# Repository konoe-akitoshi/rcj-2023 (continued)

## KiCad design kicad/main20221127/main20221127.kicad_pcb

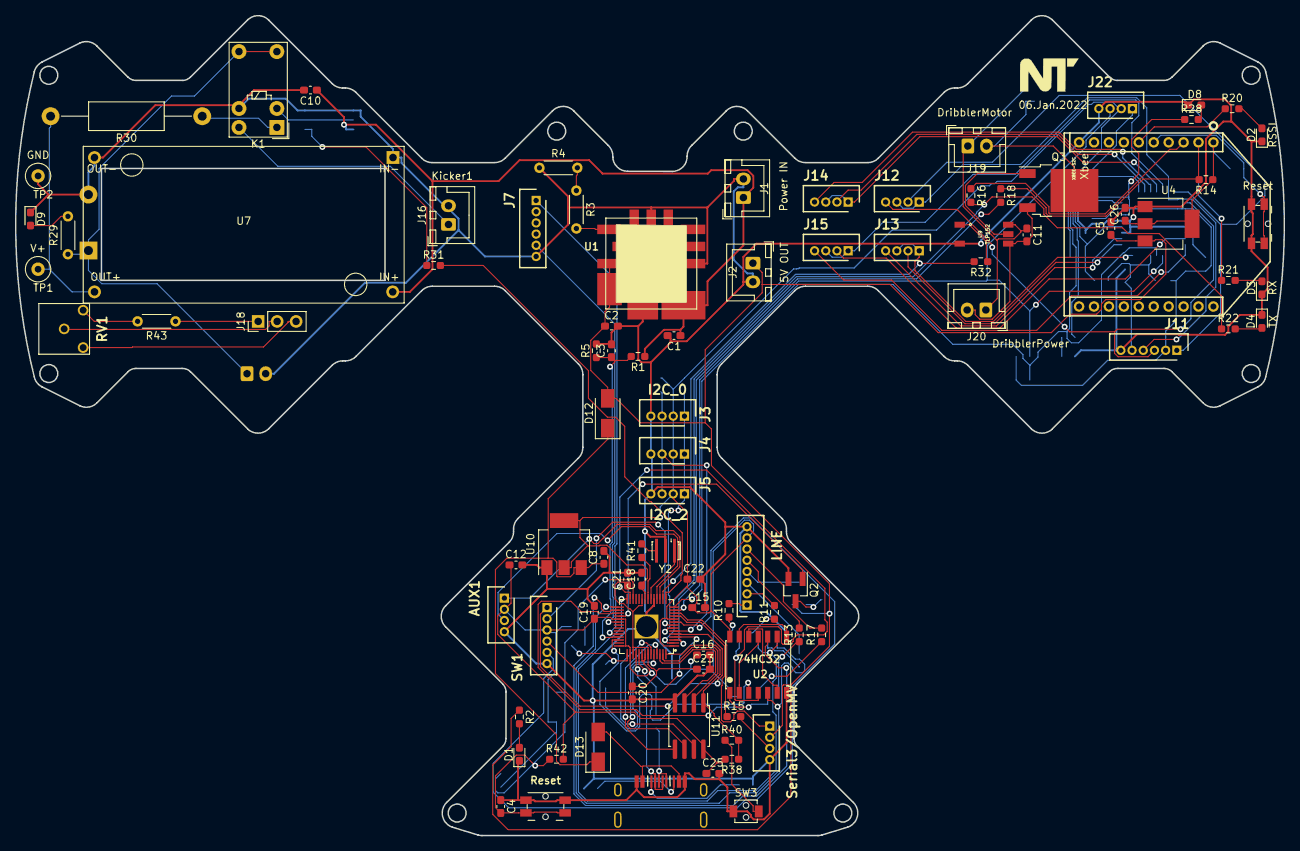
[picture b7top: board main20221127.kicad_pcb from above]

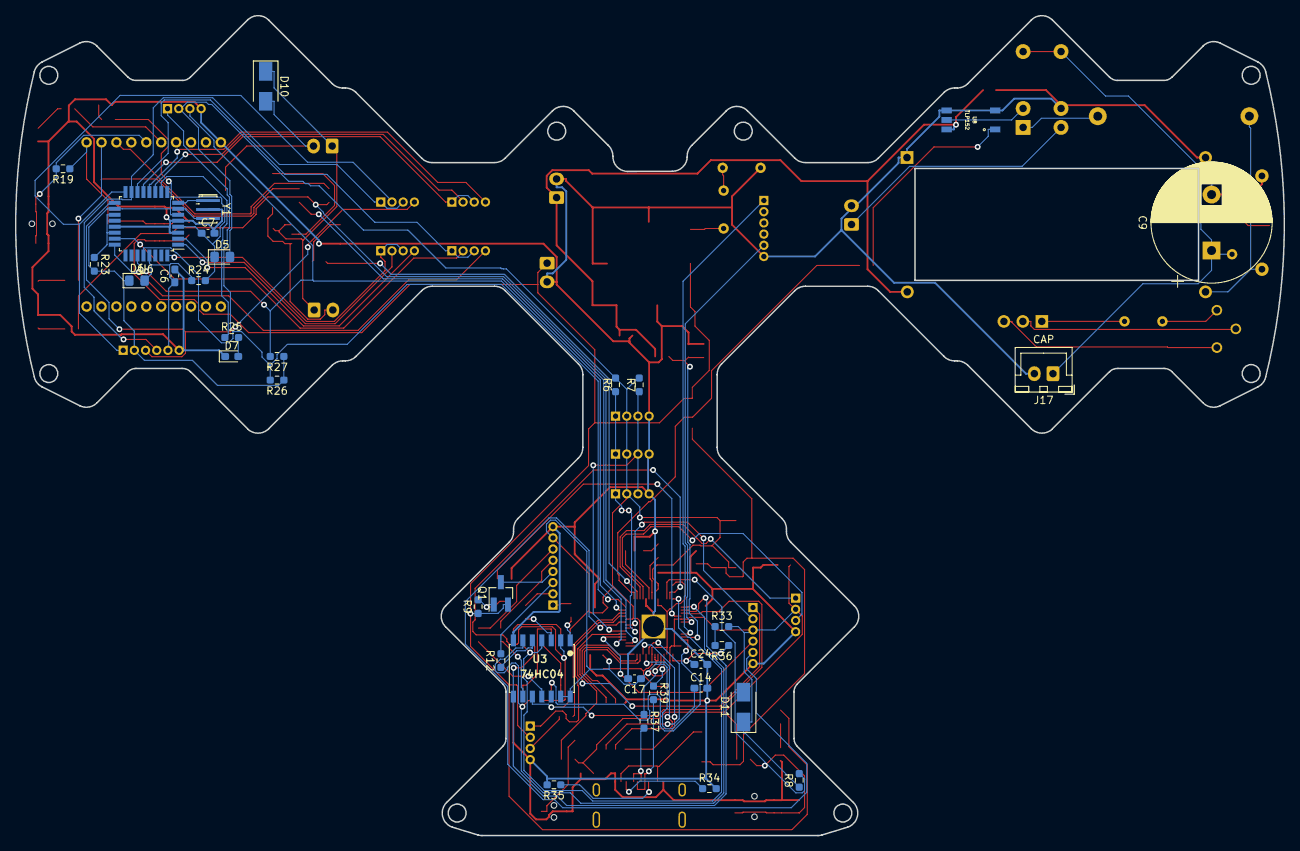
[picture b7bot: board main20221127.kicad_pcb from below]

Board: 2 copper layers, 170.0 x 109.9 mm, 127 parts (34 on the bottom side), 115 nets.

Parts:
C1, C2, C3, C4, C5, C6, C26: 10u; C_0603_1608Metric_Pad1.08x0.95mm_HandSolder
C7, C14, C15, C16, C17, C18, C19, C20, C21, C25: 0.1u; C_0603_1608Metric_Pad1.08x0.95mm_HandSolder
C8, C12: 10uF; C_0603_1608Metric_Pad1.08x0.95mm_HandSolder
C9: 2200uF/63V; CP_Radial_D16.0mm_P7.50mm
C10, C11, C22, C23, C24: 1uF; C_0603_1608Metric_Pad1.08x0.95mm_HandSolder
D1: LED; LED_SMLE13WBC8W1
D2: RSSI; LED_0603_1608Metric_Pad1.05x0.95mm_HandSolder
D3: RX; LED_0603_1608Metric_Pad1.05x0.95mm_HandSolder
D4: TX; LED_0603_1608Metric_Pad1.05x0.95mm_HandSolder
D5, D6: RSX101VAM-30TR; D_0805_2012Metric_Pad1.15x1.40mm_HandSolder
D7, D8: LED(OSWT1608); LED_0603_1608Metric_Pad1.05x0.95mm_HandSolder
D9: LED; LED_0603_1608Metric_Pad1.05x0.95mm_HandSolder
D10, D12, D13: SX34F; D_SMA
D11: RSX101VAM-30TR; D_SMA
J1: Power IN; JST_XH_B2B-XH-A_1x02_P2.50mm_Vertical
J2: 5V OUT; JST_XH_B2B-XH-A_1x02_P2.50mm_Vertical
J3: I2C_0; JSTB4B-ZR
J4: I2C_1; JSTB4B-ZR
J5: I2C_2; JSTB4B-ZR
J6: SW1; JSTB6B-ZR
J7: LED; JSTB6B-ZR
J8: AUX1; JSTB4B-ZR
J9: LINE; JSTB8B-ZR
J10: Serial3/OpenMV; JSTB4B-ZR
J11: ICSP; JSTB6B-ZR
J12: MD1; JSTB4B-ZR
J13: MD2; JSTB4B-ZR
J14: MD3; JSTB4B-ZR
J15: MD4; JSTB4B-ZR
J16: Kicker1; JST_XH_B2B-XH-A_1x02_P2.50mm_Vertical
J17: CAP; JST_XH_B2B-XH-A_1x02_P2.50mm_Vertical
J18: Conn_01x03; PinHeader_1x03_P2.54mm_Vertical
J19: DribblerMotor; JST_XH_B2B-XH-A_1x02_P2.50mm_Vertical
J20: DribblerPower; JST_XH_B2B-XH-A_1x02_P2.50mm_Vertical
J21: USB2.0_C_v3; USB-C-12-Pin-MidMount-ali-v4
J22: I2C_3; JSTB4B-ZR
K1: G5V-1/12V; Relay_SPDT_Omron_G5V-1
Q1: AO3401A; SOT-23_Handsoldering
Q2: AO3400A; SOT-23_Handsoldering
Q3: NP52N06SLG; TO-252-2
R1, R8, R23, R26, R27: 47k; R_0603_1608Metric_Pad0.98x0.95mm_HandSolder
R2, R20, R21, R22, R25, R28: 470; R_0603_1608Metric_Pad0.98x0.95mm_HandSolder
R3: 1k; R_Axial_DIN0204_L3.6mm_D1.6mm_P5.08mm_Horizontal
R4: 330; R_Axial_DIN0204_L3.6mm_D1.6mm_P5.08mm_Horizontal
R5, R6, R7, R9, R10, R11, R12, R13, R14, R15, R16, R17, R18, R19, R24: 10k; R_0603_1608Metric_Pad0.98x0.95mm_HandSolder
R29: 30k; R_Axial_DIN0204_L3.6mm_D1.6mm_P5.08mm_Horizontal
R30: 100; R_Axial_DIN0411_L9.9mm_D3.6mm_P20.32mm_Horizontal
R31, R32: 120; R_0603_1608Metric_Pad0.98x0.95mm_HandSolder
R33: 200R; R_0603_1608Metric_Pad0.98x0.95mm_HandSolder
R34, R35: 5.1kR; R_0603_1608Metric_Pad0.98x0.95mm_HandSolder
R36: 1R; R_0603_1608Metric_Pad0.98x0.95mm_HandSolder
R37, R39: 27.4R; R_0603_1608Metric_Pad0.98x0.95mm_HandSolder
R38: 10kR; R_0603_1608Metric_Pad0.98x0.95mm_HandSolder
R40: 1kR; R_0603_1608Metric_Pad0.98x0.95mm_HandSolder
R41, R42: 1k; R_0603_1608Metric_Pad0.98x0.95mm_HandSolder
R43: 200; R_Axial_DIN0204_L3.6mm_D1.6mm_P5.08mm_Horizontal
RV1: 20k; Trim-GF063X
SW1, SW2: Reset; THAU13-AB-R
SW3: BOOTSEL; TVAF06-A020B-R
TP1: V+; TestPoint_Loop_D2.60mm_Drill0.9mm_Beaded
TP2: GND; TestPoint_Loop_D2.60mm_Drill0.9mm_Beaded
U1: OKL-T_3-W12N-C; OKL-T3-W12N-C
U2: 74HC32; SOP14W
U3: 74HC04; SOP14W
U4, U10: AZ1117CH-3.3; SOT-223-3_TabPin2
U5: XBEE-S2C
U6: ATmega328P-AU; TQFP-32_7x7mm_P0.8mm
U7: XL6009/HW-432; XL6009_HW432
U8, U9: TLP152
U11: W25Q128JVS; W25Q16-128JV-SOIC
U12: RP2040; RP2040_hand
Y1: 8Mhz; Resonator_SMD_Murata_CSTxExxV-3Pin_3.0x1.1mm_HandSoldering
Y2: 12Mhz; Resonator_SMD_Murata_CSTxExxV-3Pin_3.0x1.1mm_HandSoldering

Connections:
+1V1: C20.1, C21.1, C23.1, U12.23 (DVDD), U12.45 (VREG_VOUT), U12.50 (DVDD)
+3.3VA: C7.1, D5.1 (K), D6.1 (K), J11.2, R23.2, R24.2, R26.1, R27.1, R28.1, U6.4 (VCC), U6.6 (VCC), U6.18 (AVCC)
+3V3: C12.1, C14.1, C15.1, C16.1, C17.1, C18.1, C19.1, C22.1, C25.1, D5.2 (A), D11.1 (K), J3.2, J4.2, J5.2, J6.3, J8.2, J9.7, J22.2, R6.1, R7.1, R8.1, R33.2, R38.2, R42.2, U2.14 (VCC), U3.13, U3.14 (VCC), U10.2 (VO), U11.8 (VCC), U12.1 (IOVDD), U12.10 (IOVDD), U12.22 (IOVDD), U12.33 (IOVDD), U12.42 (IOVDD), U12.44 (VREG_IN), U12.48 (USB_VDD), U12.49 (IOVDD)
+5V: C2.1, C5.1, D12.2 (A), J2.1, J10.2, Q1.2 (S), R2.1, R9.1, U1.4 (VOUT), U1.5 (SENSE), U4.3 (VI)
+15V: C1.1, C10.1, J1.1, R1.1, U1.2 (VIN), U7.2 (+VIN), U8.6 (VCC)
/Sheet61861092/drib_in: R32.2, U12.16 (GPIO13)
/Sheet61861092/kick_in: R31.2, U12.15 (GPIO12)
/Sheet63625160/SCL_1: J22.1, R26.2, U6.28 (PC5), U12.14 (GPIO11)
/Sheet63625160/SDA_1: J22.3, R27.2, U6.27 (PC4), U12.13 (GPIO10)
/rp2040/GPIO00/01: R16.2, R22.1, U12.2 (GPIO0)
/rp2040/GPIO01/02: R18.2, U12.3 (GPIO1)
/rp2040/GPIO02/04: J6.4, U12.4 (GPIO2)
/rp2040/GPIO03/05: J6.1, U12.5 (GPIO3)
/rp2040/GPIO04/06: J3.3, J4.3, J5.3, R7.2, U12.6 (GPIO4)
/rp2040/GPIO05/07: J3.1, J4.1, J5.1, R6.2, U12.7 (GPIO5)
/rp2040/GPIO06/09: J6.2, U12.8 (GPIO6)
/rp2040/GPIO07/10: J6.5, U12.9 (GPIO7)
/rp2040/GPIO08/11: J10.1, U12.11 (GPIO8)
/rp2040/GPIO09/12: R15.1, U12.12 (GPIO9)
/rp2040/GPIO14/19: J8.1, U12.17 (GPIO14)
/rp2040/GPIO15/20: J8.3, U12.18 (GPIO15)
/rp2040/GPIO16/21: U2.4, U3.2, U12.27 (GPIO16)
/rp2040/GPIO17/22: U2.9, U3.4, U12.28 (GPIO17)
/rp2040/GPIO18/24: U2.5, U3.6, U12.29 (GPIO18)
/rp2040/GPIO19/25: U2.10, U3.8, U12.30 (GPIO19)
/rp2040/GPIO20/26: U2.1, U3.10, U12.31 (GPIO20)
/rp2040/GPIO21/27: Q2.1 (G), U12.32 (GPIO21)
/rp2040/GPIO22/29: J7.5, U12.34 (GPIO22)
/rp2040/GPIO26/31: J7.1, U12.38 (GPIO26_ADC0)
/rp2040/GPIO28/34: U2.3, U12.40 (GPIO28_ADC2)
/rp2040/RUN(RES)/30: C4.2, D11.2 (A), R8.2, R42.1, SW1.1, U12.26 (RUN)
ADC_VREF: R33.1, R36.2
GND: C1.2, C2.2, C3.2, C4.1, C5.2, C6.2, C7.2, C8.2, C9.2, C10.2, C12.2, C14.2, C15.2, C16.2, C17.2, C18.2, C19.2, C20.2, C21.2, C22.2, C23.2, C24.2, C25.2, C26.2, D1.1 (K), D2.1 (K), D3.1 (K), D4.1 (K), D7.1 (K), D8.1 (K), D9.1 (K), J1.2, J2.2, J3.4, J4.4, J5.4, J6.6, J7.6, J8.4, J9.8, J10.4, J11.6, J16.2, J17.2, J21.4 (GND), J22.4, K1.9, Q2.2 (S), R4.1, R5.2, R34.2, R35.2, SW1.2, SW2.2, SW3.1, TP2.1, U1.1 (ON/OFF), U1.3 (GND_1), U1.7 (GND_2), U2.7 (GND), U3.7 (GND), U4.1 (GND), U5.10 (GND), U6.3 (GND), U6.5 (GND), U6.21 (GND), U7.1 (-VIN), U7.3 (-VOUT), U8.3, U8.4 (GND), U9.3, U10.1 (GND), U11.4 (GND), U12.19 (TESTEN), U12.57 (GND), Y1.2, Y2.2
unnamed: C6.1, D6.2 (A), J11.5, R24.1, U6.29 (~RESET/PC6)
unnamed: C8.1, D12.1 (K), D13.1 (K), U10.3 (VI)
unnamed: C9.1, J17.1, K1.5, K1.6, R29.1
unnamed: C11.1, D10.1 (K), J19.1, J20.1, U9.6 (VCC)
unnamed: C11.2, J20.2, Q3.3 (S), U9.4 (GND)
unnamed: C24.1, R36.1, U12.43 (ADC_AVDD)
unnamed: C26.1, R14.1, R19.1, U4.2 (VO), U5.1 (VDD)
unnamed: D1.2 (A), R2.2
unnamed: D2.2 (A), R20.2
unnamed: D3.2 (A), R21.2
unnamed: D4.2 (A), R22.2
unnamed: D7.2 (A), R25.2
unnamed: D8.2 (A), R28.2
unnamed: D9.2 (A), R29.2
unnamed: D10.2 (A), J19.2, Q3.2 (D)
unnamed: D13.2 (A), J21.1 (VBUS)
unnamed: J9.1, R10.2
unnamed: J9.2, R11.2
unnamed: J9.3, R12.2
unnamed: J9.4, Q1.3 (D)
unnamed: J9.5, R13.2
unnamed: J9.6, R17.2
unnamed: J10.3, R15.2
unnamed: J11.1, J12.2, U6.16 (PB4)
unnamed: J11.3, J12.4, U6.17 (PB5)
unnamed: J11.4, J12.1, J12.3, U6.15 (PB3)
unnamed: J13.1, J13.3, U6.32 (PD2)
unnamed: J13.2, U6.1 (PD3)
unnamed: J13.4, U6.2 (PD4)
unnamed: J14.1, J14.3, U6.13 (PB1)
unnamed: J14.2, U6.11 (PD7)
unnamed: J14.4, U6.12 (PB0)
unnamed: J15.1, J15.3, U6.14 (PB2)
unnamed: J15.2, U6.23 (PC0)
unnamed: J15.4, U6.24 (PC1)
unnamed: J16.1, K1.10
unnamed: J18.1, R43.1
unnamed: J18.2, RV1.2
unnamed: J18.3, RV1.3
unnamed: J21.5 (CC1), R35.1
unnamed: J21.6 (CC2), R34.1
unnamed: K1.1, R30.1
unnamed: K1.2, U8.5 (VO)
unnamed: Q1.1 (G), Q2.3 (D), R9.2
unnamed: Q3.1 (G), U9.5 (VO)
unnamed: R3.1, R4.2
unnamed: R3.2, U1.6 (TRIM)
unnamed: R10.1, U3.1
unnamed: R11.1, U3.3
unnamed: R12.1, U3.5
unnamed: R13.1, U3.9
unnamed: R14.2, R18.1, R21.1, U5.2 (DOUT)
unnamed: R16.1, U5.3 (DIN)
unnamed: R17.1, U3.11
unnamed: R19.2, SW2.1, U5.5 (RESET)
unnamed: R20.1, U5.6 (RSSI)
unnamed: R23.1, U6.19 (ADC6), U6.22 (ADC7)
unnamed: R25.1, U6.10 (PD6)
unnamed: R30.2, TP1.1, U7.4 (+VOUT)
unnamed: R31.1, U8.1
unnamed: R32.1, U9.1
unnamed: R37.1, U12.47 (USB_DP)
unnamed: R39.1, U12.46 (USB_DM)
unnamed: R40.1, SW3.2
unnamed: R41.1, U12.21 (XOUT)
unnamed: R41.2, Y2.3
unnamed: R43.2, RV1.1
unnamed: U2.2, U2.11
unnamed: U2.6, U2.12
unnamed: U2.8, U2.13
unnamed: U6.7 (XTAL1/PB6), Y1.3
unnamed: U6.8 (XTAL2/PB7), Y1.1
unnamed: U12.20 (XIN), Y2.1
QSPI_CLK: U11.6 (CLK), U12.52 (QSPI_SCLK)
QSPI_SD0: U11.5 (DI(IO0)), U12.53 (QSPI_SD0)
QSPI_SD1: U11.2 (DO(IO1)), U12.55 (QSPI_SD1)
QSPI_SD2: U11.3 (IO2), U12.54 (QSPI_SD2)
QSPI_SD3: U11.7 (IO3), U12.51 (QSPI_SD3)
QSPI_SS: R38.1, R40.2, U11.1 (~CS), U12.56 (QSPI_SS)
USB_DM: J21.2 (D-), R39.2
USB_DP: J21.3 (D+), R37.2
Vbatt: C3.1, R1.2, R5.1, U12.39 (GPIO27_ADC1)

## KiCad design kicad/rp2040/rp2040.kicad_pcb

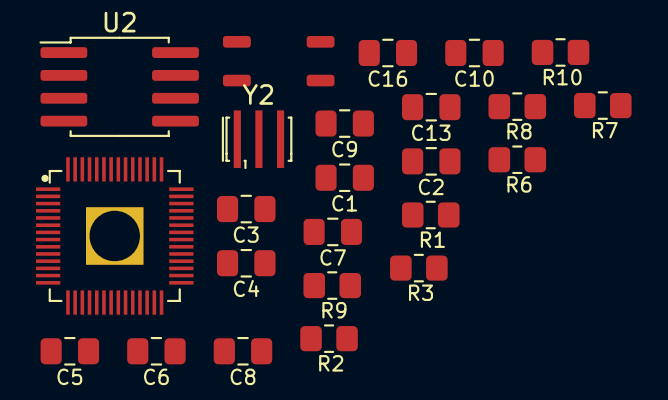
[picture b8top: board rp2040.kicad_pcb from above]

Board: 2 copper layers, 24 parts (0 on the bottom side), 18 nets, no tracks yet.

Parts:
C1, C2, C4, C6, C7, C8, C10, C13, C16: 100nF; Capacitor_0805_2012
C3, C5, C9: 1uF; Capacitor_0805_2012
R1, R2: 27.4R; Register_0805_2012
R3, R6, R7: 1kR; Register_0805_2012
R8: 10kR; Register_0805_2012
R9: 200R; Register_0805_2012
R10: 1R; Register_0805_2012
SW1: SW_Push; SKRPABE010
U1: RP2040; RP2040_hand
U2: W25Q128JVS; W25Q16-128JV-SOIC
Y2: 12Mhz; Resonator_SMD_Murata_CSTxExxV-3Pin_3.0x1.1mm_HandSoldering

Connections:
+1V1: C1.1, C2.1, C3.1, U1.23 (DVDD), U1.45 (VREG_VOUT), U1.50 (DVDD)
+3V3: C4.1, C5.1, C6.1, C7.1, C8.1, C10.1, C13.1, C16.1, R7.2, R8.2, R9.2, U1.1 (IOVDD), U1.10 (IOVDD), U1.22 (IOVDD), U1.33 (IOVDD), U1.42 (IOVDD), U1.44 (VREG_IN), U1.48 (USB_VDD), U1.49 (IOVDD), U2.8 (VCC)
/RUN(RES)/30: R7.1, U1.26 (RUN)
ADC_VREF: R9.1, R10.2
GND: C1.2, C2.2, C3.2, C4.2, C5.2, C6.2, C7.2, C8.2, C9.2, C10.2, C13.2, C16.2, SW1.1, U1.19 (TESTEN), U1.57 (GND), U2.4 (GND), Y2.2
unnamed: C9.1, R10.1, U1.43 (ADC_AVDD)
unnamed: R1.1, U1.47 (USB_DP)
unnamed: R2.1, U1.46 (USB_DM)
unnamed: R3.1, SW1.2
unnamed: R6.1, U1.21 (XOUT)
unnamed: R6.2, Y2.3
unnamed: U1.20 (XIN), Y2.1
QSPI_CLK: U1.52 (QSPI_SCLK), U2.6 (CLK)
QSPI_SD0: U1.53 (QSPI_SD0), U2.5 (DI(IO0))
QSPI_SD1: U1.55 (QSPI_SD1), U2.2 (DO(IO1))
QSPI_SD2: U1.54 (QSPI_SD2), U2.3 (IO2)
QSPI_SD3: U1.51 (QSPI_SD3), U2.7 (IO3)
QSPI_SS: R3.2, R8.1, U1.56 (QSPI_SS), U2.1 (~CS)

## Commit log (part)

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2022-11-04 originaldata
2022-11-07 chore: update README.md
2022-11-07 chore: fix typo in README.md
2022-11-08 refactor: rename main program directory
    ディレクトリの階層も変更してる
2022-11-08 chore: add .gitignore
2022-11-08 style: format by clang-format
2022-11-08 style: fix format by manual
2022-11-10 pcb rp2040test
2022-11-11 Tof 基板起こし
2022-11-14 chore: delete kicad
2022-11-16 chore: add local include files
2022-11-16 fix: lsp diagnostic error
    Program.cpp is a file for editing.
    In clangd, *.ino files could not be treated as cpp files even if `set filetype=cpp`.
2022-11-16 refactor: remove unused global variable `Vstep`
2022-11-16 refactor: move `Pmax` from global to local
2022-11-16 refactor: move `i` to for-local
2022-11-16 perf: for-loop `i` should use before increment
2022-11-16 refactor: change the type of `emergency`
2022-11-16 refactor: change the type of `outofbounds`
    Is this variable is used?
2022-11-16 refactor: change the type of `lineflag`
2022-11-16 chore: Sorry, I forgot to reflect cpp to ino
    Program.cpp を Program.ino に反映させました。本来は1つのコミットで同時に行うべきでした。
    (寝る直前にいじってるから、思考力低下してたみたいです。。ごめんなさい)
2022-11-16 refactor: move (x|y|h|w)_data_.*(ball|goal) to local
2022-11-16 refactor: move global `Pcontrol` to local
2022-11-16 fix: type of`Pmax`
    5380feb6130a1f7105fe9b19619264285087dbac
2022-11-16 refactor: move global `az` to local
2022-11-16 refactor: move global `fx`, `fy` to local
2022-11-16 refactor: remove unused global
    - `level`: int
    - `ball_x`: int
    - `ball_y`: int
    - `buf`: char[]
2022-11-17 refactor: remove unused variables
    - `h`: int
    - `w`: int
    - `area`: int
    - `(bg|yg)_h`: int
    - `(bg|yg)_w`: int
    - `(bg|yg)_area`: int
2022-11-17 feat: create `LedLight` class and replace with it.
    replaced:
    - NATIVE_LED
    - LINE_LED
    - LED_R
    - LED_Y
    - LED_G
2022-11-17 refactor: 3.14 to PI
2022-11-17 fix: local include guard
2022-11-17 style: format
2022-11-17 perf: global `Kp` `Ki` `Kd` to constexpr
2022-11-17 refactor: remove unused global `outofbounds`
2022-11-17 refactor: change the variable init-pos from setup to declaration
2022-11-17 chore: update comment
2022-11-18 refactor: move `ball_dir` from global to local
2022-11-18 refactor: move `data_diff` from global to local
2022-11-18 refactor move `kick` form global to static local
2022-11-18 feat: create struct `Vector2` and replace with it
    replaced:
    - `blue_goal` (bg_x, bg_y)
    - `yellow_goal` (yg_x, yg_y)
    - `goal` (goal_x, goal_y)
    - `xbee` (xbee_x, xbee_y)
2022-11-18 refactor: move `goal` from global to local
2022-11-20 refactor: move global `z` to local, remove unused `m`
2022-11-20 refactor: move global `gyro` to local
    also, changed the type from float to int.
    because Serial2.read() returns int.
    https://github.com/PaulStoffregen/cores/blob/HEAD/teensy3/HardwareSerial.h#L334-L370
2022-11-21 refactor: `*_sig` is rename to `exist_*_gola`
    Also, its type is changed from float to bool.
    Giving python script which send the openMV data, the type of `*_sig` is int. And also, in this context, this value is used for checking. So boolean is good.
2022-11-22 refactor: remove unnecessary openmv files
2022-11-22 feat!: combine to `xbee_data` to `ball_dist`
2022-11-22 feat: Vector2 static method `squareNorm` `norm`
    also, added operator
2022-11-22 refactor: `x` `y` to `ball_pos`
2022-11-24 fix: compile error
2022-11-28 kicad main+kick-drib
2022-11-28 fix: main xbee
2022-12-01 power
2022-12-21 no message
2022-12-26 add gyro program
2022-12-27 feat: add components `OpenMV`
2022-12-27 refactor: remove meaningless code for `lineflag`
    ref
    - 05be307a8a21a64df17ab2cb551cc3c2730265b5
    - 4d9c16b8bb96f3d34a7926fb809d37569474fbdb
    (cherry picked from commit c8aa26dab87c78a293293eca75584e3cbe45ce32)
2022-12-27 feat: new component `XBee`
    (cherry picked from commit 4733240a76fc848ae55c840ef61b59b49a4295bc)
2022-12-27 feat: new component `Battery`
    (cherry picked from commit 4699e2b4999bde448e71dabc2c241de3f2212596)
2022-12-27 perf: pin value, const -> constexpr
2022-12-27 refactor: rename pin name
2022-12-27 refactor: change to early return in loop()
2022-12-27 refactor: remove unnecessary code
2022-12-28 refactor: organize pin part1
2022-12-28 refactor: organize pin part2
2022-12-28 refactor: organize pin part3
2022-12-28 refactor: simplify `motorfunction``
2022-12-29 style: update coding style
2022-12-29 feat!: remove `dribbler2`
2022-12-29 feat: new component `Dribbler`
2022-12-29 refactor: update `setup()`
2022-12-29 refactor: update `loop()`
2022-12-29 refactor: rename Line LED -> Line Sensor LED
2022-12-29 refactor: use enum `GoalType` for goal switch flag
2022-12-29 feat: new component `Kicker`
2022-12-29 feat: new component `DigitalReader`
2022-12-29 refactor: organize
2022-12-29 feat!: remove `lineflag`
2022-12-29 feat!: remove `Wire` module
2022-12-29 refactor: add global variable `rotation`
2022-12-30 refactor: rename openmv python file
2022-12-30 chore: update gitignore
2022-12-30 refactor: remove unused import `image`
2022-12-30 Revert "feat: `MotorContoroler.Drive` can omit power arg and set default power by `SetPower()`"
    This reverts commit 5702e7335ccec78334d3916c4223c59dcaaecf13.
2022-12-30 refactor: rename `p_ball` to `pair_ball_dist`
2022-12-30 chore: add doc comment
2022-12-31 refactor: rename
2022-12-31 chore: rename and remove file
2023-01-01 add: 328p program
2023-01-03 feat: rewrite main algorithm
2023-01-03 fix: motor_controller2 did not reverse
2023-01-03 chore: ready for mainprogram test
2023-01-04 perf: change FPS limit
2023-01-04 feat!: remove `SetupHandler::SetupHandler`, use `SetCallback`
2023-01-04 feat: add `SerialReader`
2023-01-04 test: `util::SerialReader`
2023-01-04 test: `std::pair` (pair<int,int> is used in `component::SetupHandler`
2023-01-04 test: `component::LedLight`
2023-01-04 test: `component::SetupHandler`
2023-01-04 test: `component::Motor`
2023-01-04 feat: new component `Gyro`
2023-01-05 fix: numerical adjustment of color detect
2023-01-05 refactor: generalize serial communication
2023-01-06 fix: fix serial communication
2023-01-06 feat: add test function
2023-01-06 chore: update local include files
2023-01-06 feat: upgrade to new `component::Gyro`
2023-01-06 feat: Serial3 -> Serial2 in `components::OpenMV`
2023-01-07 style: arrange code
2023-01-07 feat: upgrade pin
2023-01-07 fix: `MotorController` does not work
2023-01-07 test: `component::Kicker`
2023-01-07 Revert "feat: upgrade to new `component::Gyro`"
    new Gyro does not work (maybe hardware issue)
    So, Change to use old gyro.
    Since we are not going to use the XBee this time, we decided to use its free Serial port to run the old Gyro.
    Commit of that change will follow.
2023-01-07 feat!: use old gyro
    ref: ddc3c607bb456d1c180c1e44c28461f4f1f1522b
2023-01-08 test: `component::Dribbler`
2023-01-08 eat: new component `DigitalReaderPCF8575`
2023-01-08 feat: rewrite interruptHandler()
2023-01-08 feat: new component `LedLightPCF8574`
2023-01-08 test: `component::LedLightPCF8574`
2023-01-08 Revert pin
2023-01-08 Revert MotorController
2023-01-08 fix: Gyro
2023-01-08 refactor: create sample generator
2023-01-08 fix: Gyro (2)
2023-01-08 feat: add mkdir
2023-01-08 feat: upgrade to `component::OpenCV`
2023-01-08 fix: pin name
2023-01-08 refactor: create hsv_range optimizer
2023-01-08 fix: fix variable error
2023-01-08 fix: fix small bugs
2023-01-08 feat: add function to save results
2023-01-08 test: `component::Gyro`
2023-01-08 feat: you can set HIGH or LOW when you tern on LED
2023-01-08 test: check for robot can chase the ball
2023-02-02 some
2023-02-15 feat!: clean up all main program code part 1
2023-02-15 feat!: clean up all main program code part 2
2023-02-20 fix: on_transmit
2023-02-20 feat: add overclock.py
2023-02-20 feat!: clean up all main program code part 3
2023-02-20 fix: I2C test python program
2023-02-20 test: add I2C_slave
2023-02-24 fix:
2023-02-26 update: m1n-vison
2023-02-27 refactor: create LineSensors class
2023-02-27 feat: upgrade motor programs
    - rewrite motor program into /Motor/Program/Program.ino
    - i2c send/receive data type is changed from byte[6] to byte[4]
2023-03-01 main bus
2023-03-01 buckup
2023-03-01 fix:VL6180ToF date
2023-03-01 fix: vison-boad
2023-03-01 Add GND to Wio pin14
2023-03-01 update: main
2023-03-01 SW-LED changed
2023-03-01 LED_BUILTIN -> GPIO25
2023-03-02 fix: 配線前
2023-03-02 add: typec step
2023-03-02 fix: vison-board 配線後
2023-03-02 Modify Wio coneector
2023-03-02 fix: power
2023-03-02 fix: power step
2023-03-02 Power基板できた
2023-03-02 MMA LOGO
2023-03-03 配線 標準
2023-03-03 PCB 修正
2023-03-03 未配線 ２か所
2023-03-03 fix: 配線後
2023-03-03 fix: main 発注ファイル
2023-03-04 add: step
2023-03-07 fix: motor does not free
2023-03-07 test: clean up Vison-M1n tests
2023-03-07 test: add Vison-M1n tests
2023-03-07 add: xbee-gyro
2023-03-07 Step file
2023-03-09 test: line sensor interrupt check
2023-03-09 feat: add camera calibration program
2023-03-13 test: add test of multi camera field of view check
2023-03-13 fix: MultiCameraView runtime error
2023-03-13 test: add camera rp2040 i2c scanner program
2023-03-13 refoactor: use main() and add comment to calibration program
2023-03-13 feat: add opencv perspective transform program
2023-03-14 refactor: use lowerCamelCase in cpp function
2023-03-14 feat: camera calibration reverse map
2023-03-15 perf: reduce variable type size
2023-03-15 fix: m1n runtime error
2023-03-15 test: read Gyro data
2023-03-15 fix: Gyro use UART0
2023-03-15 fix: create_reverse_map
2023-03-15 feat: Gyro reset rotation
2023-03-15 feat: implement camera calibration
2023-03-15 test: ToF Sensor
2023-03-15 feat: fill Camera Matrix
2023-03-15 fix: Line Sensor LED pin number
2023-03-16 fix: index error on Calibration calc
2023-03-16 refactor: move CameraController class definition to more deep dir
2023-03-16 feat: add module::MainWire
2023-03-16 feat: add module::Camera for main, remove module::OpenCV
2023-03-17 refactor: remap array size reduction
2023-03-19 feat: add I2CManager for main
    Wire are used by multiple modules. I2CManager manage Wire setup.
2023-03-19 test: battery emergency check
2023-03-19 test: add.CameraController test
2023-03-19 test: motion of stepped line
2023-03-19 test: main LED check
2023-03-20 feat: add setup check request
2023-03-20 fix: LED light does not work correctry
2023-03-20 test: MotorController
2023-03-20 fix: order of setting i2c callback
2023-03-20 feat: wait for camera's setup in camera pico
2023-03-20 test: add motor values test
2023-03-21 feat: add Camera Matrix
2023-03-21 feat: reduce i2c send data
2023-03-21 test: add move to ball test
2023-03-21 fix: use Wire1
2023-03-21 refactor: move fixBySectionSeparate to camera's python program
2023-03-21 feat: add i2c frequency setting
2023-03-21 refactor: remove debug mode
2023-03-22 chore: add wio terminal develop env
2023-03-22 feat!: not use wio terminal
2023-03-22 perf: use const
2023-03-22 fix: object existance check is broken
2023-03-23 fix: goal width
2023-03-23 feat: use int in param `power` of MotorController::drive
2023-03-23 fix: does not update goal width
2023-03-23 test: ToFSensor require setScaling
    From library source code, the default Scaling is 1. But if ommit setScaling, the reading value is broken
2023-03-23 feat: create new attacker algorith
2023-03-23 feat: impliment terminal
2023-03-23 feat: add module::Terminal for main
2023-03-23 fix: syntax error and format
2023-03-23 refactor: use attack/defence goal in global in stead of blue/yellow goal
2023-03-23 refactor: remove global type enum, use local flag
2023-03-24 fix: goal width are overflow
2023-03-24 feat: enhance terminal ui
2023-03-24 fix: Camera Matrix
2023-03-24 feat: enhance machine status display/light
2023-03-24 fix: ToF sensor does not work collectly
    よくわからないけど、setBusしたら治った。治った後コメントアウトして再度書き込んでも治ってた。
    もしかしたらデフォルト値でも再度指定すると正しく動作するようになるのかもしれない。
2023-03-24 fix: typo tern -> turn
2023-03-24 test: XBee send/read check
2023-03-24 feat: upgrade main program
2023-03-24 cleanup unused program
2023-03-24 rename filename
